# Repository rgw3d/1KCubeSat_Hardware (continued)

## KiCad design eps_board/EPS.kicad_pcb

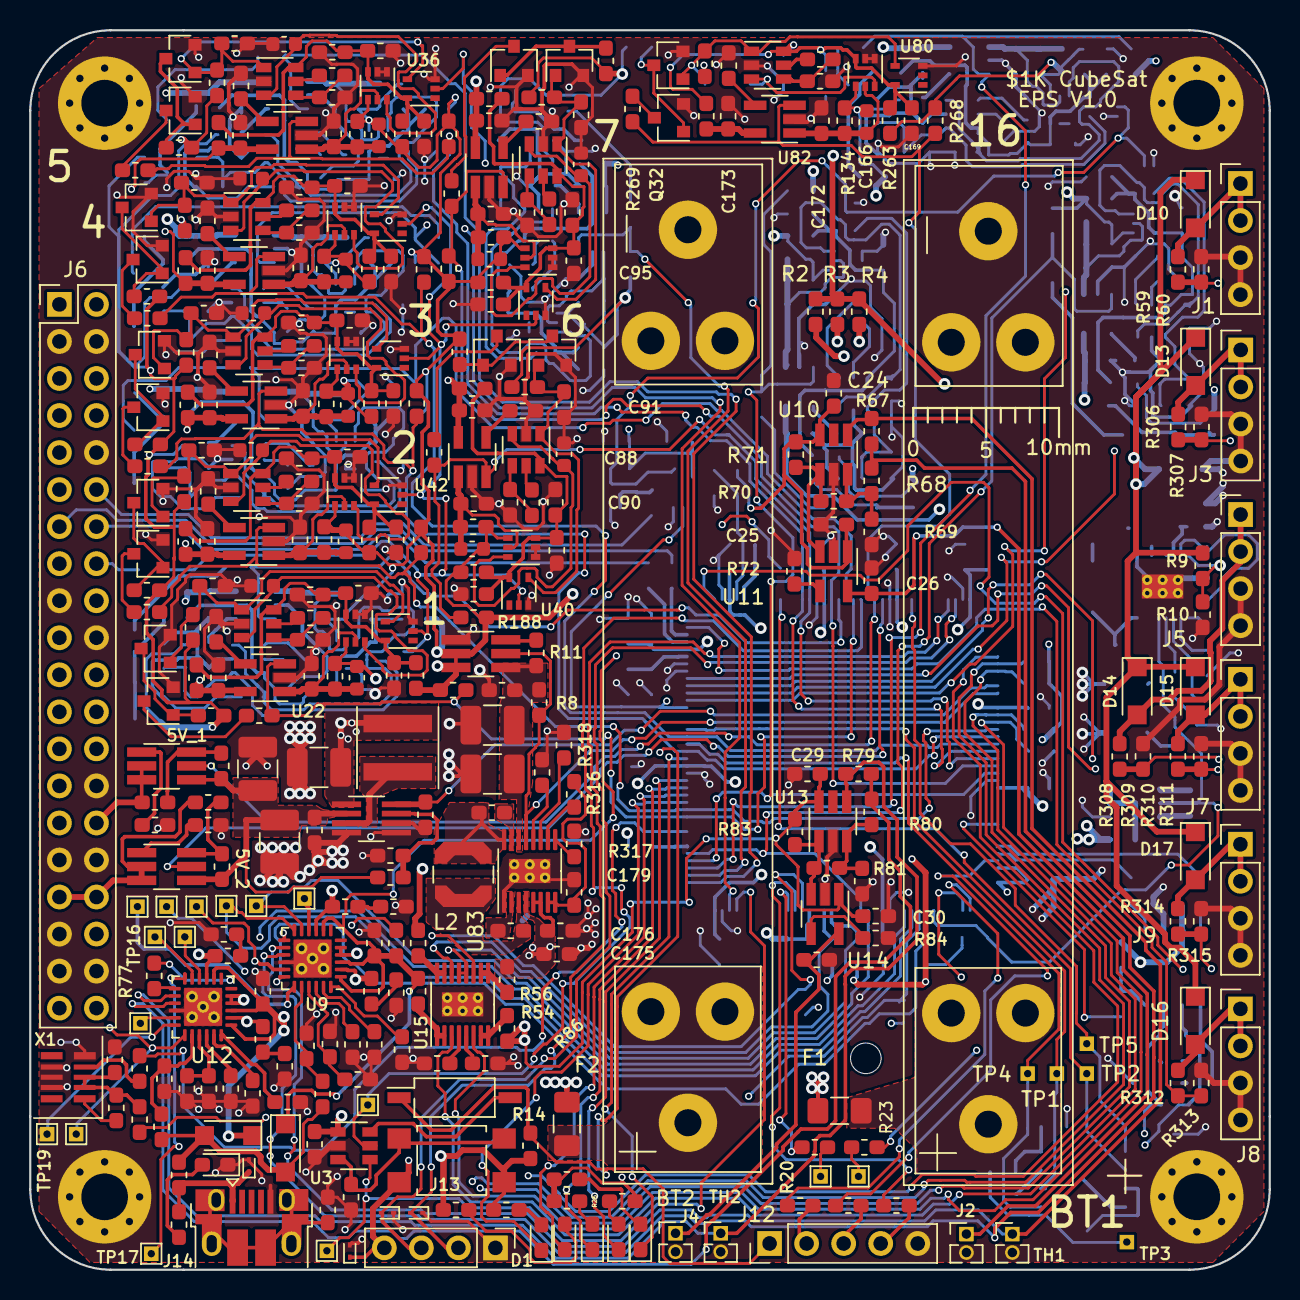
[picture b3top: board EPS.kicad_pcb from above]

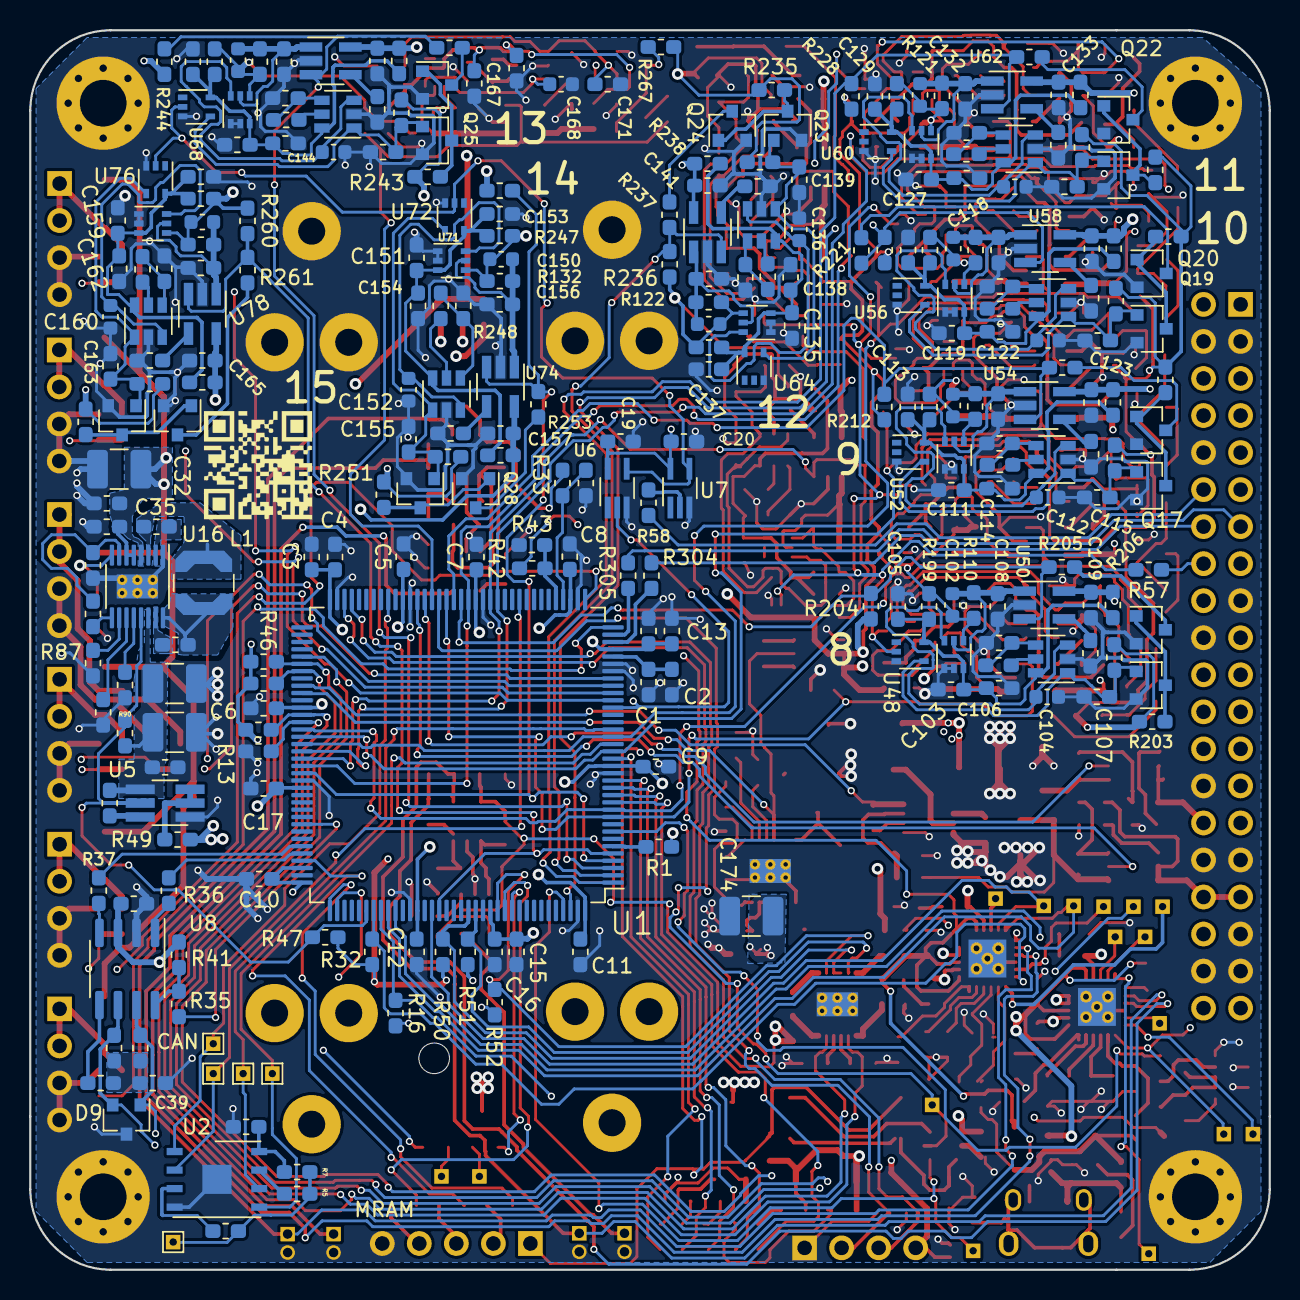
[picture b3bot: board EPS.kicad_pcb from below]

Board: 4 copper layers, 85.0 x 85.0 mm, 656 parts (279 on the bottom side), 356 nets.

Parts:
BT1, BT2: Battery_Cell; BatteryHolder_Keystone_54_v2_1x18650
C1, C2, C13: 0.01uF; C_0603_1608Metric_Pad1.05x0.95mm_HandSolder
C3, C15, C22, C25, C27, C30, C33, C40, C52, C60, C68, C76, C84, C92, C100, C108, C116, C124, C132, C140, C148, C156, C164, C172, C175, C179, C187, C188, C189, C190, C191, C192: 4.7uF; C_0603_1608Metric_Pad1.05x0.95mm_HandSolder
C4, C5, C6, C7, C8, C9, C10, C11, C12, C16, C17, C18, C19, C20, C21, C24, C26, C29, C31, C36, C38, C47, C49, C50, C53, C55, C57, C58, C61, C63, C65, C66, C69, C71, C73, C74, C77, C79, C81, C82, C85, C87, C89, C90, C93, C95, C97, C98, C101, C103, C105, C106, C109, C111, C113, C114, C117, C119, C121, C122, C125, C127, C129, C130, C133, C135, C137, C138, C141, C143, C145, C146, C149, C151, C153, C154, C157, C159, C161, C162, C165, C167, C169, C170, C173: 0.1uF; C_0603_1608Metric_Pad1.05x0.95mm_HandSolder
C14, C34, C44, C45, C51, C59, C67, C75, C83, C91, C99, C107, C115, C123, C131, C139, C147, C155, C163, C171, C176, C184: 1uF; C_0603_1608Metric_Pad1.05x0.95mm_HandSolder
C23, C28, C43, C182: DNP; C_0603_1608Metric_Pad1.05x0.95mm_HandSolder
C32, C41, C174, C180, C183, C185: 47uF; C_1210_3225Metric_Pad1.42x2.65mm_HandSolder
C35, C37, C177, C178: 22nF; C_0603_1608Metric_Pad1.05x0.95mm_HandSolder
C39: 4.7nF; C_0603_1608Metric_Pad1.05x0.95mm_HandSolder
C42, C181, C186: DNP; C_1210_3225Metric_Pad1.42x2.65mm_HandSolder
C46, C48, C54, C56, C62, C64, C70, C72, C78, C80, C86, C88, C94, C96, C102, C104, C110, C112, C118, C120, C126, C128, C134, C136, C142, C144, C150, C152, C158, C160, C166, C168: DNP; C_0603_1608Metric
D1, D19: LED_SMD_RED; LED_0603_1608Metric_Pad1.05x0.95mm_HandSolder
D2: LED_SMD_GREEN; LED_0603_1608Metric_Pad1.05x0.95mm_HandSolder
D3, D4, D5: LED_SMD_YELLOW; LED_0603_1608Metric_Pad1.05x0.95mm_HandSolder
D6, D7, D8, D18: ESD9B5.0ST5G; D_SOD-923
D9: NUP2105L; SOT-23
D10, D11, D12, D13, D14, D15, D16, D17: NRVB120VLSFT1G; D_SOD-123FL_handsolder
F1, F2: Polyfuse; Fuse_1206_3216Metric_Pad1.42x1.75mm_HandSolder
FID4: Fiducial; Gauge_10mm_Type1_SilkScreenTop
H1: MountingHole; MountingHole_2.1mm
H2, H3, H4, H5: MountingHole_Pad; MountingHole_3.2mm_M3_Pad_Via
J1, J3, J5, J7, J8, J9: Conn_01x04; PinHeader_1x04_P2.54mm_Vertical
J2, J4: Conn_01x02_Female; PinHeader_1x02_P1.27mm_Vertical
J6: Conn_02x20_Odd_Even; PinHeader_2x20_P2.54mm_Vertical
J12: Conn_01x05; PinHeader_1x05_P2.54mm_Vertical
J13: Conn_01x04_Male; PinHeader_1x04_P2.54mm_Vertical
J14: USB_B_Micro; USB_Micro-B_Amphenol_10103594-0001LF_Horizontal
L1, L2: 4.7uH; L_Coilcraft_LPS4018
L3: 2.2uH; L_Coilcraft_XAL5030
Q1, Q2, Q3, Q4, Q5, Q6, Q7, Q8, Q9, Q10, Q11, Q12, Q13, Q14, Q15, Q16, Q17, Q18, Q19, Q20, Q21, Q22, Q23, Q24, Q25, Q26, Q27, Q28, Q29, Q30, Q31, Q32: 2N7002K; SOT-23
R1, R29, R30, R31, R35, R36, R37, R38, R57, R58, R87, R88, R89, R90, R143, R149, R151, R157, R159, R165, R167, R173, R175, R181, R183, R189, R191, R197, R199, R205, R207, R213, R215, R221, R223, R229, R231, R237, R239, R245, R247, R253, R255, R261, R263, R269, R304, R305, R316, R317, R318, R319, R327: 0; R_0603_1608Metric_Pad1.05x0.95mm_HandSolder
R2, R3, R4, R7, R49, R53, R54, R55, R56, R328: 10m; R_0603_1608Metric_Pad1.05x0.95mm_HandSolder
R5, R6, R8, R10, R12, R13, R14, R16, R17, R18, R32, R33, R41, R42, R46, R47, R50, R51, R52, R59, R60, R65, R68, R77, R80, R144, R152, R160, R168, R176, R184, R192, R200, R208, R216, R224, R232, R240, R248, R256, R264, R306, R307, R308, R309, R310, R311, R312, R313, R314, R315, R320: 100K; R_0603_1608Metric_Pad1.05x0.95mm_HandSolder
R9: 224K; R_0603_1608Metric_Pad1.05x0.95mm_HandSolder
R11, R48, R62, R64, R66, R67, R74, R76, R78, R79, R97, R98: 10K; R_0603_1608Metric_Pad1.05x0.95mm_HandSolder
R15: 8.85K; R_0603_1608Metric_Pad1.05x0.95mm_HandSolder
R19, R20, R21, R22, R23: 49.9; R_0603_1608Metric_Pad1.05x0.95mm_HandSolder
R24, R25, R26, R27, R28, R329: 330; R_0603_1608Metric_Pad1.05x0.95mm_HandSolder
R34, R43: 150K; R_0603_1608Metric_Pad1.05x0.95mm_HandSolder
R39, R40: 60.4; R_0603_1608Metric_Pad1.05x0.95mm_HandSolder
R61, R73: 26.7K; R_0603_1608Metric_Pad1.05x0.95mm_HandSolder
R63, R71, R75, R83, R145, R147, R148, R153, R155, R156, R161, R163, R164, R169, R171, R172, R177, R179, R180, R185, R187, R188, R193, R195, R196, R201, R203, R204, R209, R211, R212, R217, R219, R220, R225, R227, R228, R233, R235, R236, R241, R243, R244, R249, R251, R252, R257, R259, R260, R265, R267, R268, R321: 1M; R_0603_1608Metric_Pad1.05x0.95mm_HandSolder
R69, R81: 280K; R_0603_1608Metric_Pad1.05x0.95mm_HandSolder
R70, R82, R150, R158, R166, R174, R182, R190, R198, R206, R214, R222, R230, R238, R246, R254, R262, R270: DNP; R_0603_1608Metric_Pad1.05x0.95mm_HandSolder
R72, R84, R100, R102, R104, R106, R112, R114, R116, R118, R124, R126, R128, R130, R136, R138, R140, R142: 3.09K; R_0603_1608Metric_Pad1.05x0.95mm_HandSolder
R85, R86: 150; R_0603_1608Metric_Pad1.05x0.95mm_HandSolder
R91, R92: 1K; R_0603_1608Metric_Pad1.05x0.95mm_HandSolder
R93, R95, R96, R107, R108, R109, R110, R119, R120, R121, R122, R131, R132, R133, R134: 0.1; R_0603_1608Metric_Pad1.05x0.95mm_HandSolder
R94: 0.039; R_0603_1608Metric_Pad1.05x0.95mm_HandSolder
R99: 20K; R_0603_1608Metric_Pad1.05x0.95mm_HandSolder
R101, R103, R105, R123, R125, R127, R129, R135, R137, R139, R141: 140K; R_0603_1608Metric_Pad1.05x0.95mm_HandSolder
R111, R117: 698K; R_0603_1608Metric_Pad1.05x0.95mm_HandSolder
R113, R115: 1.5M; R_0603_1608Metric_Pad1.05x0.95mm_HandSolder
R322: 137K; R_0603_1608Metric_Pad1.05x0.95mm_HandSolder
R323, R324, R325, R326: 1; R_0603_1608Metric_Pad1.05x0.95mm_HandSolder
SW1: SW_DIP_x01; SW_DIP_SPSTx01_Slide_Copal_CHS-01B_W7.62mm_P1.27mm
SW2: SW_Push; SW_SPST_TL3305A
TH1, TH2: Thermistor_NTC; PinHeader_1x02_P1.27mm_Vertical
TP1, TP2, TP3, TP4, TP5, TP8, TP9: TP_smt_1x1; TestPoint_THTPad_1.0x1.0mm_Drill0.5mm
TP7, TP10, TP11, TP12, TP13, TP14, TP15, TP16, TP17, TP18, TP19, TP20: TP_1x1; TestPoint_THTPad_1.0x1.0mm_Drill0.5mm
TP37, TP39: TP_1.5x1.5; TestPoint_THTPad_1.0x1.0mm_Drill0.5mm
U1: STM32L496ZGTx; LQFP-144_20x20mm_P0.5mm
U2: MR25H10; DFN-8-1EP_6x5mm_P1.27mm_EP2x2mm
U3: TPL5010; SOT-23-6
U4, U5, U17, U18: TPS270; TSOT-23-6_HandSoldering
U6, U7: 74LVC1G07; SOT-353_SC-70-5_Handsoldering
U8: SN65HVD230; SOIC-8_3.9x4.9mm_P1.27mm
U9, U12: LTC4066; QFN-24-1EP_4x4mm_P0.5mm_EP2.6x2.6mm_0.4mmThermalVias
U10, U13: MCP65R46; SOT-23-6_Handsoldering
U11, U14, U22, U26, U30, U34, U38, U42, U46, U50, U54, U58, U62, U66, U70, U74, U78, U82: FPF2123; SOT-23-5_HandSoldering
U15: LTC4415; MSOP-16-1EP_3x4.039mm_P0.5mm_EP1.651x2.845mm_0.3mmThermalVi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
U16, U83: LTC3130-1; MSOP-16-1EP_3x4.039mm_P0.5mm_EP1.651x2.845mm_0.3mmThermalVi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
U19, U23, U27, U31, U35, U39, U43, U47, U51, U55, U59, U63, U67, U71, U75, U79: NCS211; SOT-363_SC-70-6
U20, U24, U28, U32, U36, U40, U44, U48, U52, U56, U60, U64, U68, U72, U76, U80: 74LVC1G07; SOT-353_SC-70-5
U21, U25, U29, U33, U37, U41, U45, U49, U53, U57, U61, U65, U69, U73, U77, U81: MCP65R46; SOT-23-6
U84: MP3414A; TSOT-23-8_HandSoldering
X1: TG-3541CE; Oscillator_SMD_SeikoEpson_TG3541CE-10Pin_3.2x2.5mm_HandSold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

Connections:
+3V3: C19.2, C20.2, C46.2, C54.2, C62.2, C70.2, C78.2, C86.2, C94.2, C102.2, C110.2, C118.2, C126.2, C134.2, C142.2, C150.2, C158.2, C166.2, R93.2, R94.2, R95.2, R96.2, R107.2, R108.2, R109.2, R110.2, R119.2, R120.2, R121.2, R122.2, R131.2, R132.2, R133.2, R134.2, R143.2, R145.2, R147.2, R148.2, R151.2, R153.2, R155.2, R156.2, R159.2, R161.2, R163.2, R164.2, R167.2, R169.2, R171.2, R172.2, R175.2, R177.2, R179.2, R180.2, R183.2, R185.2, R187.2, R188.2, R191.2, R193.2, R195.2, R196.2, R199.2, R201.2, R203.2, R204.2, R207.2, R209.2, R211.2, R212.2, R215.2, R217.2, R219.2, R220.2, R223.2, R225.2, R227.2, R228.2, R231.2, R233.2, R235.2, R236.2, R239.2, R241.2, R243.2, R244.2, R247.2, R249.2, R251.2, R252.2, R255.2, R257.2, R259.2, R260.2, R263.2, R265.2, R267.2, R268.2, U4.2, U4.3, U6.5, U7.5, U19.4, U23.4, U27.4, U31.4, U35.4, U39.4, U43.4, U47.4, U51.4, U55.4, U59.4, U63.4, U67.4, U71.4, U75.4, U79.4
+5V: C184.1, C185.1, C186.1, R97.2, R98.2, R321.2, U17.4, U18.4, U84.2
/3.3V_9: C117.2, J6.9, R214.1, U54.5
/3.3V_10: C125.2, J6.6, R222.1, U58.5
/3.3V_11: C133.2, J6.1, R230.1, U62.5
/3.3V_12: C141.2, J6.18, R238.1, U66.5
/3.3V_16: C173.2, R270.1, U82.5
/3.3V_ACS_LOGIC: C85.2, J6.2, R182.1, U38.5
/3.3V_AVI_CAN: C77.2, J6.5, R174.1, U34.5
/3.3V_CLK: C109.2, J6.25, R206.1, U50.5
/3.3V_EPS_CAN: C38.1, C157.2, R41.1, R254.1, U8.3, U74.5
/3.3V_EPS_MRAM: C165.2, R5.1, R6.1, R7.2, R262.1, TP3.1, U78.5
/3.3V_EPS_STM: C21.1, C149.2, D6.1, J13.4, R2.1, R3.1, R4.1, R12.2, R14.1, R16.2, R18.2, R24.1, R25.1, R26.1, R27.1, R28.1, R30.2, R32.2, R46.2, R47.2, R50.1, R51.1, R52.1, R246.1, SW2.1, U3.1, U70.5
/3.3V_GPS: C61.2, J6.24, R158.1, U26.5
/3.3V_GYRO: C93.2, J6.23, R190.1, U42.5
/3.3V_MAG: C101.2, J6.8, R198.1, U46.5
/3.3V_MRAM: C69.2, J6.11, R166.1, U30.5
/3.3V_STM_CORE: C53.2, J6.26, R150.1, U22.5
/5V0_1: C44.1, J6.30, U17.2, U17.3
/5V0_2: C45.1, J6.33, J6.34, U18.2, U18.3
/AVI_EXTRN_RST: R57.2, U20.2, U24.2, U28.2, U32.2, U36.2, U40.2, U44.2, U48.2
/BATTERY/NTC: R67.2, TH1.1, U9.14, U10.4
/BATTERY/VNTC: R67.1, R68.1, U9.15
/BATTERY_CHARGER/BAT: C189.1, F1.1, U9.2, U9.4, U9.5
/BC_1_CLDIS: TP7.1, U9.10
/BC_1_ISTAT: R66.2, U9.24
/BC_1_POL: R46.1, TP12.1, U1.78, U9.19
/BC_1_SHDN: TP11.1, U1.117, U9.12
/BC_1_SUSP: TP10.1, U1.123, U9.11
/BC_2_CLDIS: TP15.1, U12.10
/BC_2_ISTAT: R78.2, U12.24
/BC_2_POL: R18.1, TP18.1, U1.79, U12.19
/BC_2_SHDN: TP17.1, U1.118, U12.12
/BC_2_SUSP: TP16.1, U1.77, U12.11
/CANH: D9.1, J6.40, R39.1, U8.7
/CANL: D9.2, J6.39, R40.2, U8.6
/CURRENT_MONITORS/PWR1_8_ON: R204.1, R205.1, U1.54, U50.3
/CURRENT_MONITORS/PWR1_9_ON: R212.1, R213.1, U1.55, U54.3
/CURRENT_MONITORS/PWR1_10_ON: R220.1, R221.1, U1.142, U58.3
/CURRENT_MONITORS/PWR1_11_ON: R228.1, R229.1, U1.1, U62.3
/CURRENT_MONITORS/PWR1_12_ON: R236.1, R237.1, U1.2, U66.3
/CURRENT_MONITORS/PWR1_13_ON: R244.1, R245.1, U1.3, U70.3
/CURRENT_MONITORS/PWR1_16_ON: R268.1, R269.1, U1.58, U82.3
/CURRENT_MONITORS/PWR2_1_ON: U1.59, U17.5
/CURRENT_MONITORS/PWR2_2_ON: U1.60, U18.5
/CURRENT_MONITORS/RST1_13: U6.4, U7.4, U68.2, U72.2, U76.2
/CURRENT_MONITORS/sheet601A160D/ISET+: R100.2, U22.4
/CURRENT_MONITORS/sheet601A160D/RREF+: R99.2, U21.5
/CURRENT_MONITORS/sheet601A160D/RREF-: R99.1, R144.2, U21.4
/CURRENT_MONITORS/sheet601A160D/SHUNT-: C46.1, C52.2, R93.1, U19.5, U22.1
/CURRENT_MONITORS/sheet620B1C5A/ISET+: R138.2, U74.4
/CURRENT_MONITORS/sheet620B1C5A/RREF+: R137.2, U73.5
/CURRENT_MONITORS/sheet620B1C5A/RREF-: R137.1, R248.2, U73.4
/CURRENT_MONITORS/sheet620B1C5A/SHUNT-: C150.1, C156.2, R132.1, U71.5, U74.1
/CURRENT_MONITORS/sheet620B1C5B/ISET+: R140.2, U78.4
/CURRENT_MONITORS/sheet620B1C5B/RREF+: R139.2, U77.5
/CURRENT_MONITORS/sheet620B1C5B/RREF-: R139.1, R256.2, U77.4
/CURRENT_MONITORS/sheet620B1C5B/SHUNT-: C158.1, C164.2, R133.1, U75.5, U78.1
/CURRENT_MONITORS/sheet620B1C5C/ISET+: R142.2, U82.4
/CURRENT_MONITORS/sheet620B1C5C/RREF+: R141.2, U81.5
/CURRENT_MONITORS/sheet620B1C5C/RREF-: R141.1, R264.2, U81.4
/CURRENT_MONITORS/sheet620B1C5C/SHUNT-: C166.1, C172.2, R134.1, U79.5, U82.1
/CURRENT_MONITORS/sheet620B1C59/ISET+: R136.2, U70.4
/CURRENT_MONITORS/sheet620B1C59/RREF+: R135.2, U69.5
/CURRENT_MONITORS/sheet620B1C59/RREF-: R135.1, R240.2, U69.4
/CURRENT_MONITORS/sheet620B1C59/SHUNT-: C142.1, C148.2, R131.1, U67.5, U70.1
/CURRENT_MONITORS/sheet6206D7D7/ISET+: R106.2, U34.4
/CURRENT_MONITORS/sheet6206D7D7/RREF+: R105.2, U33.5
/CURRENT_MONITORS/sheet6206D7D7/RREF-: R105.1, R168.2, U33.4
/CURRENT_MONITORS/sheet6206D7D7/SHUNT-: C70.1, C76.2, R96.1, U31.5, U34.1
/CURRENT_MONITORS/sheet6209BA5A/ISET+: R128.2, U62.4
/CURRENT_MONITORS/sheet6209BA5A/RREF+: R127.2, U61.5
/CURRENT_MONITORS/sheet6209BA5A/RREF-: R127.1, R224.2, U61.4
/CURRENT_MONITORS/sheet6209BA5A/SHUNT-: C126.1, C132.2, R121.1, U59.5, U62.1
/CURRENT_MONITORS/sheet6209BA5B/ISET+: R130.2, U66.4
/CURRENT_MONITORS/sheet6209BA5B/RREF+: R129.2, U65.5
/CURRENT_MONITORS/sheet6209BA5B/RREF-: R129.1, R232.2, U65.4
/CURRENT_MONITORS/sheet6209BA5B/SHUNT-: C134.1, C140.2, R122.1, U63.5, U66.1
/CURRENT_MONITORS/sheet6209BA58/ISET+: R124.2, U54.4
/CURRENT_MONITORS/sheet6209BA58/RREF+: R123.2, U53.5
/CURRENT_MONITORS/sheet6209BA58/RREF-: R123.1, R208.2, U53.4
/CURRENT_MONITORS/sheet6209BA58/SHUNT-: C110.1, C116.2, R119.1, U51.5, U54.1
/CURRENT_MONITORS/sheet6209BA59/ISET+: R126.2, U58.4
/CURRENT_MONITORS/sheet6209BA59/RREF+: R125.2, U57.5
/CURRENT_MONITORS/sheet6209BA59/RREF-: R125.1, R216.2, U57.4
/CURRENT_MONITORS/sheet6209BA59/SHUNT-: C118.1, C124.2, R120.1, U55.5, U58.1
/CURRENT_MONITORS/sheet62057B58/ISET+: R104.2, U30.4
/CURRENT_MONITORS/sheet62057B58/RREF+: R103.2, U29.5
/CURRENT_MONITORS/sheet62057B58/RREF-: R103.1, R160.2, U29.4
/CURRENT_MONITORS/sheet62057B58/SHUNT-: C62.1, C68.2, R95.1, U27.5, U30.1
/CURRENT_MONITORS/sheet6204228E/ISET+: R102.2, U26.4
/CURRENT_MONITORS/sheet6204228E/RREF+: R101.2, U25.5
/CURRENT_MONITORS/sheet6204228E/RREF-: R101.1, R152.2, U25.4
/CURRENT_MONITORS/sheet6204228E/SHUNT-: C54.1, C60.2, R94.1, U23.5, U26.1
/CURRENT_MONITORS/sheet6208477B/ISET+: R112.2, U38.4
/CURRENT_MONITORS/sheet6208477B/RREF+: R111.2, U37.5
/CURRENT_MONITORS/sheet6208477B/RREF-: R111.1, R176.2, U37.4
/CURRENT_MONITORS/sheet6208477B/SHUNT-: C78.1, C84.2, R107.1, U35.5, U38.1
/CURRENT_MONITORS/sheet6208477C/ISET+: R114.2, U42.4
/CURRENT_MONITORS/sheet6208477C/RREF+: R113.2, U41.5
/CURRENT_MONITORS/sheet6208477C/RREF-: R113.1, R184.2, U41.4
/CURRENT_MONITORS/sheet6208477C/SHUNT-: C86.1, C92.2, R108.1, U39.5, U42.1
/CURRENT_MONITORS/sheet6208477D/ISET+: R116.2, U46.4
/CURRENT_MONITORS/sheet6208477D/RREF+: R115.2, U45.5
/CURRENT_MONITORS/sheet6208477D/RREF-: R115.1, R192.2, U45.4
/CURRENT_MONITORS/sheet6208477D/SHUNT-: C94.1, C100.2, R109.1, U43.5, U46.1
/CURRENT_MONITORS/sheet6208477E/ISET+: R118.2, U50.4
/CURRENT_MONITORS/sheet6208477E/RREF+: R117.2, U49.5
/CURRENT_MONITORS/sheet6208477E/RREF-: R117.1, R200.2, U49.4
/CURRENT_MONITORS/sheet6208477E/SHUNT-: C102.1, C108.2, R110.1, U47.5, U50.1
/EPS_EXTRN_RST: R58.2, U7.2
/EPS_WATCHDOG: J12.1, R14.2, SW1.1, U1.25, U6.2
/HPWR_EN: R320.2, U1.81, U84.8
/IDEAL_EN1: R12.1, U1.85, U15.3
/INTERBOARD_CONNECTOR/AVI_RESET: J6.16, R57.1
/INTERBOARD_CONNECTOR/EPS_RESET: J6.12, R58.1
/PG_3V3: R8.1, U1.82, U4.5, U83.13
/PG_SOLAR: R17.1, R47.1, U1.114, U5.5, U16.13
/PMIC/ADC1_IN9: R33.2, R34.2, U1.40
/PMIC/ADC1_IN10: R42.2, R43.2, U1.41
/PMIC/CAN1_RX: R37.2, U1.103
/PMIC/CAN1_TX: R36.2, U1.104
/PMIC/CAN_RS: R35.2, U1.100
/PMIC/CAN_TRANSCEIVER/Vref: R38.2, U8.5
/PMIC/INT_1: R148.1, R149.1, U1.10, U1.56, U22.3
/PMIC/INT_2: R156.1, R157.1, U1.11, U1.87, U26.3
/PMIC/INT_3: R164.1, R165.1, U1.19, U1.88, U30.3
/PMIC/INT_4: R172.1, R173.1, U1.21, U1.89, U34.3
/PMIC/INT_5: R180.1, R181.1, U1.49, U1.90, U38.3
/PMIC/INT_6: R188.1, R189.1, U1.50, U1.91, U42.3
/PMIC/INT_7: R196.1, R197.1, U1.53, U1.92, U46.3
/PMIC/INT_8: R252.1, R253.1, U1.4, U1.93, U74.3
/PMIC/INT_9: R260.1, R261.1, U1.5, U1.124, U78.3
/PMIC/JTCK_SWCLK: R20.1, U1.109
/PMIC/JTDI: R23.1, U1.110
/PMIC/JTDO_TRACESWO: R22.1, U1.133
/PMIC/JTMS_SWDIO: R21.1, U1.105
/PMIC/LED_1: D1.1, U1.12
/PMIC/LED_2: D2.1, U1.13
/PMIC/LED_3: D3.1, U1.14
/PMIC/LED_4: D4.1, U1.15
/PMIC/LED_5: D5.1, U1.18
/PMIC/LPUART1_RX: D8.2, J13.2, U1.69
/PMIC/LPUART1_TX: D7.2, J13.3, U1.70
/PMIC/NJRST: R19.1, U1.134
/PMIC/OSC32_TCXO/OE: R31.1, X1.1
/PMIC/QUADSPI_BK1_IO0: TP4.1, U1.20, U2.5
/PMIC/QUADSPI_BK1_IO1: TP2.1, U1.46, U2.2
/PMIC/QUADSPI_BK1_NCS: TP5.1, U1.64, U2.1
/PMIC/QUADSPI_CLK: TP1.1, U1.22, U2.6
/PMIC/RCC_OSC32_IN: R29.2, U1.8
/PMIC/UART4_RX: R305.2, U1.35
/PMIC/UART4_TX: R304.2, U1.34
/PMIC/WATCHDOG_DONE: TP9.1, U1.141, U3.4
/PMIC/WATCHDOG_WAKE: TP8.1, U1.57, U3.5
/SOLAR_5V: C187.1, C190.1, R49.1, U9.9, U12.9
/SOLAR_ADC1: R59.2, R60.1, U1.26
/SOLAR_ADC2: R306.2, R307.1, U1.27
/SOLAR_ADC3: R308.2, R309.1, U1.28
/SOLAR_ADC4: R310.2, R311.1, U1.29
/SOLAR_ADC5: R312.2, R313.1, U1.36
/SOLAR_ADC6: R314.2, R315.1, U1.37
/SOLAR_MPPT_5V/MPPC: R9.2, R10.2, U16.8
/SOLAR_MPPT_5V/VCC: C40.1, R88.2, U16.7
/SOLAR_MPPT_5V/VOUT: C41.1, C42.1, C43.1, R17.2, R48.2, U5.4, U16.14
/UART_RXI: J6.13, R305.1
/UART_TXO: J6.14, R304.1
/VEXT: D11.2, D12.2, R61.2, R73.2, R328.1
/VOUT1: C24.1, C25.1, C188.1, D11.1, R33.1, R53.2, R65.2, R71.1, U9.1, U9.3, U9.8, U10.6, U11.1
/VOUT2: C29.1, C30.1, C191.1, D12.1, R42.1, R54.2, R77.2, R83.1, U12.1, U12.3, U12.8, U13.6, U14.1
/VRAW_SOLAR: C32.1, C33.1, C34.1, D10.1, D13.1, D14.1, D15.1, D16.1, D17.1, R9.1, U16.4, U16.5, U16.6
/sheet5F4CFCDE/BAT: C192.1, F2.1, U12.2, U12.4, U12.5
/sheet5F4CFCDE/NTC: R79.2, TH2.1, U12.14, U13.4
/sheet5F4CFCDE/VNTC: R79.1, R80.1, U12.15
/sheet5F71F776/VIN1: R53.1, U15.1, U15.2
/sheet5F71F776/VIN2: R54.1, U15.7, U15.8
/sheet5F71F776/VOUT1: R55.2, U15.15, U15.16
/sheet5F71F776/VOUT2: R56.2, U15.9, U15.10
/sheet5FCD3934/MPPC: C179.1, R316.2, U83.7, U83.8
/sheet5FCD3934/VOUT: C180.1, C181.1, C182.1, R8.2, R11.2, U4.4, U83.14
/~BC_1_CHRG: R32.1, TP13.1, U1.115, U9.18
/~BC_1_VEXT: TP14.1, U9.17
/~BC_2_CHRG: R16.1, TP19.1, U1.116, U12.18
/~BC_2_VEXT: TP20.1, U12.17
/~IDEAL_EN2: R13.2, U1.86, U15.6
/~IDEAL_STATUS1: R51.2, U1.129, U15.14
/~IDEAL_STATUS2: R52.2, U1.132, U15.11
/~IDEAL_WARN1: R50.2, U1.128, U15.12, U15.13
GND: BT1.2, BT2.2, C1.1, C2.1, C3.1, C4.2, C5.2, C6.2, C7.2, C8.2, C9.2, C10.2, C11.1, C12.1, C13.2, C14.2, C15.1, C16.1, C17.1, C18.2, C19.1, C20.1, C21.2, C22.2, C23.2, C24.2, C25.2, C26.2, C27.2, C28.2, C29.2, C30.2, C31.2, C32.2, C33.2, C34.2, C36.2, C38.2, C39.2, C40.2, C41.2, C42.2, C43.2, C47.2, C48.1, C49.1, C50.1, C51.1, C52.1, C53.1, C55.2, C56.1, C57.1, C58.1, C59.1, C60.1, C61.1, C63.2, C64.1, C65.1, C66.1, C67.1, C68.1, C69.1, C71.2, C72.1, C73.1, C74.1, C75.1, C76.1, C77.1, C79.2, C80.1, C81.1, C82.1, C83.1, C84.1, C85.1, C87.2, C88.1, C89.1, C90.1, C91.1, C92.1, C93.1, C95.2, C96.1, C97.1, C98.1, C99.1, C100.1, C101.1, C103.2, C104.1, C105.1, C106.1, C107.1, C108.1, C109.1, C111.2, C112.1, C113.1, C114.1, C115.1, C116.1, C117.1, C119.2, C120.1, C121.1, C122.1, C123.1, C124.1, C125.1, C127.2, C128.1, C129.1, C130.1, C131.1, C132.1, C133.1, C135.2, C136.1, C137.1, C138.1, C139.1, C140.1, C141.1, C143.2, C144.1, C145.1, C146.1, C147.1, C148.1, C149.1, C151.2, C152.1, C153.1, C154.1, C155.1, C156.1, C157.1, C159.2, C160.1, C161.1, C162.1, C163.1, C164.1, C165.1, C167.2, C168.1, C169.1, C170.1, C171.1, C172.1, C173.1, C174.2, C175.2, C176.2, C179.2, C180.2, C181.2, C182.2, C183.2, C184.2, C185.2, C186.2, C188.2, C191.2, D6.2, D7.1, D8.1, D9.3, D18.2, D19.1, H2.1, H3.1, H4.1, H5.1, J1.3, J1.4, J2.2, J3.3, J3.4, J4.2, J5.3, J5.4, J6.3, J6.4, J6.10, J6.17, J6.20, J6.28, J6.31, J6.32, J6.35, J6.37, J6.38, J7.3, J7.4, J8.3, J8.4, J9.3, J9.4, J12.5, J13.1, J14.5, Q1.2, Q2.2, Q3.2, Q4.2, Q5.2, Q6.2, Q7.2, Q8.2, Q9.2, Q10.2, Q11.2, Q12.2, Q13.2, Q14.2, Q15.2, Q16.2, Q17.2, Q18.2, Q19.2, Q20.2, Q21.2, Q22.2, Q23.2, Q24.2, Q25.2, Q26.2, Q27.2, Q28.2, Q29.2, Q30.2, Q31.2, Q32.2, R10.1, R13.1, R15.2, R34.1, R43.1, R60.2, R62.1, R63.1, R64.1, R66.1, R69.2, R72.1, R74.1, R75.1, R76.1, R78.1, R81.2, R84.1, R85.2, R86.2, R87.2, R89.2, R90.1, R91.1, R92.1, R100.1, R102.1, R104.1, R106.1, R112.1, R114.1, R116.1, R118.1, R124.1, R126.1, R128.1, R130.1, R136.1, R138.1, R140.1, R142.1, R144.1, R152.1, R160.1, R168.1, R176.1, R184.1, R192.1, R200.1, R208.1, R216.1, R224.1, R232.1, R240.1, R248.1, R256.1, R264.1, R307.2, R309.2, R311.2, R313.2, R315.2, R317.2, R318.2, R319.1, R320.1, R322.1, R323.2, R324.1, R325.2, R326.1, R327.1, TH1.2, TH2.2, U1.16, U1.30, U1.31, U1.38, U1.51, U1.61, U1.71, U1.83, U1.94, U1.107, U1.120, U1.130, U1.143, U2.4, U2.9, U3.2, U4.1, U5.1, U6.3, U7.3, U8.2, U9.16, U9.25, U10.2, U11.2, U12.16, U12.25, U13.2, U14.2, U15.17, U16.1, U16.17, U19.1, U19.2, U20.3, U21.2, U22.2, U23.1, U23.2, U24.3, U25.2, U26.2, U27.1, U27.2, U28.3, U29.2, U30.2, U31.1, U31.2, U32.3, U33.2, U34.2, U35.1, U35.2, U36.3, U37.2, U38.2, U39.1, U39.2, U40.3, U41.2, U42.2, U43.1, U43.2, U44.3, U45.2, U46.2, U47.1, U47.2, U48.3, U49.2, U50.2, U51.1, U51.2, U52.3, U53.2, U54.2, U55.1, U55.2, U56.3, U57.2, U58.2, U59.1, U59.2, U60.3, U61.2, U62.2, U63.1, U63.2, U64.3, U65.2, U66.2, U67.1, U67.2, U68.3, U69.2, U70.2, U71.1, U71.2, U72.3, U73.2, U74.2, U75.1, U75.2, U76.3, U77.2, U78.2, U79.1, U79.2, U80.3, U81.2, U82.2, U83.1, U83.17, U84.4, U84.5, U84.6, X1.5, X1.7, X1.8, X1.9
unnamed: BT1.1, F1.2
unnamed: BT2.1, F2.2
unnamed: C1.2, C2.2, U1.32
unnamed: C3.2, C4.1, C5.1, C6.1, C7.1, C8.1, C9.1, C10.1, C11.2, C12.2, R1.2, R2.2, U1.17, U1.39, U1.52, U1.62, U1.72, U1.84, U1.106, U1.108, U1.121, U1.144
unnamed: C13.1, C14.1, R3.2, U1.33
unnamed: C15.2, C16.2, C17.2, R4.2, U1.95, U1.131
unnamed: C18.1, R7.1, U2.8
unnamed: C22.1, C23.1, U9.21
unnamed: C26.1, J2.1, U11.5
unnamed: C27.1, C28.1, U12.21
unnamed: C31.1, J4.1, U14.5
unnamed: C35.1, L1.1, U16.3
unnamed: C35.2, U16.2
unnamed: C36.1, R30.1, R31.2, X1.2, X1.3
unnamed: C37.1, U16.15
unnamed: C37.2, L1.2, U16.16
unnamed: C39.1, R38.1, R39.2, R40.1
unnamed: C44.2, R97.1, U17.6
unnamed: C45.2, R98.1, U18.6
unnamed: C47.1, C49.2, C50.2, R143.1, R150.2, U19.3, U20.5, U21.6
unnamed: C48.2, U19.6, U21.3
unnamed: C51.2, Q1.1, R145.1, U20.4, U21.1
unnamed: C55.1, C57.2, C58.2, R151.1, R158.2, U23.3, U24.5, U25.6
unnamed: C56.2, U23.6, U25.3
unnamed: C59.2, Q3.1, R153.1, U24.4, U25.1
unnamed: C63.1, C65.2, C66.2, R159.1, R166.2, U27.3, U28.5, U29.6
unnamed: C64.2, U27.6, U29.3
unnamed: C67.2, Q5.1, R161.1, U28.4, U29.1
unnamed: C71.1, C73.2, C74.2, R167.1, R174.2, U31.3, U32.5, U33.6
unnamed: C72.2, U31.6, U33.3
unnamed: C75.2, Q7.1, R169.1, U32.4, U33.1
unnamed: C79.1, C81.2, C82.2, R175.1, R182.2, U35.3, U36.5, U37.6
unnamed: C80.2, U35.6, U37.3
unnamed: C83.2, Q9.1, R177.1, U36.4, U37.1
unnamed: C87.1, C89.2, C90.2, R183.1, R190.2, U39.3, U40.5, U41.6
unnamed: C88.2, U39.6, U41.3
unnamed: C91.2, Q11.1, R185.1, U40.4, U41.1
unnamed: C95.1, C97.2, C98.2, R191.1, R198.2, U43.3, U44.5, U45.6
unnamed: C96.2, U43.6, U45.3
unnamed: C99.2, Q13.1, R193.1, U44.4, U45.1
unnamed: C103.1, C105.2, C106.2, R199.1, R206.2, U47.3, U48.5, U49.6
unnamed: C104.2, U47.6, U49.3
unnamed: C107.2, Q15.1, R201.1, U48.4, U49.1
unnamed: C111.1, C113.2, C114.2, R207.1, R214.2, U51.3, U52.5, U53.6
unnamed: C112.2, U51.6, U53.3
unnamed: C115.2, Q17.1, R209.1, U52.4, U53.1
unnamed: C119.1, C121.2, C122.2, R215.1, R222.2, U55.3, U56.5, U57.6
unnamed: C120.2, U55.6, U57.3
unnamed: C123.2, Q19.1, R217.1, U56.4, U57.1
unnamed: C127.1, C129.2, C130.2, R223.1, R230.2, U59.3, U60.5, U61.6
unnamed: C128.2, U59.6, U61.3
unnamed: C131.2, Q21.1, R225.1, U60.4, U61.1
unnamed: C135.1, C137.2, C138.2, R231.1, R238.2, U63.3, U64.5, U65.6
unnamed: C136.2, U63.6, U65.3
unnamed: C139.2, Q23.1, R233.1, U64.4, U65.1
unnamed: C143.1, C145.2, C146.2, R239.1, R246.2, U67.3, U68.5, U69.6
unnamed: C144.2, U67.6, U69.3
unnamed: C147.2, Q25.1, R241.1, U68.4, U69.1
unnamed: C151.1, C153.2, C154.2, R247.1, R254.2, U71.3, U72.5, U73.6
unnamed: C152.2, U71.6, U73.3
unnamed: C155.2, Q27.1, R249.1, U72.4, U73.1
unnamed: C159.1, C161.2, C162.2, R255.1, R262.2, U75.3, U76.5, U77.6
unnamed: C160.2, U75.6, U77.3
unnamed: C163.2, Q29.1, R257.1, U76.4, U77.1
unnamed: C167.1, C169.2, C170.2, R263.1, R270.2, U79.3, U80.5, U81.6
unnamed: C168.2, U79.6, U81.3
unnamed: C171.2, Q31.1, R265.1, U80.4, U81.1
unnamed: C177.1, L2.1, U83.3
unnamed: C177.2, U83.2
unnamed: C178.1, U83.15
unnamed: C178.2, L2.2, U83.16
unnamed: C187.2, R323.1
unnamed: C189.2, R324.2
unnamed: C190.2, R325.1
unnamed: C192.2, R326.2
unnamed: D1.2, R24.2
unnamed: D2.2, R25.2
unnamed: D3.2, R26.2
unnamed: D4.2, R27.2
unnamed: D5.2, R28.2
unnamed: D10.2, J1.1, J1.2, R59.1
unnamed: D13.2, J3.1, J3.2, R306.1
unnamed: D14.2, J5.1, J5.2, R308.1
unnamed: D15.2, J7.1, J7.2, R310.1
unnamed: D16.2, J8.1, J8.2, R312.1
unnamed: D17.2, J9.1, J9.2, R314.1
unnamed: D18.1, J14.1, R328.2, R329.2
unnamed: D19.2, R329.1
unnamed: J12.2, R20.2
unnamed: J12.3, R21.2
unnamed: J12.4, R22.2
unnamed: J14.6, R327.2
unnamed: L3.1, U84.3
unnamed: Q1.3, Q2.1, R147.1
unnamed: Q2.3, R149.2
unnamed: Q3.3, Q4.1, R155.1
unnamed: Q4.3, R157.2
unnamed: Q5.3, Q6.1, R163.1
unnamed: Q6.3, R165.2
unnamed: Q7.3, Q8.1, R171.1
unnamed: Q8.3, R173.2
unnamed: Q9.3, Q10.1, R179.1
unnamed: Q10.3, R181.2
unnamed: Q11.3, Q12.1, R187.1
unnamed: Q12.3, R189.2
unnamed: Q13.3, Q14.1, R195.1
unnamed: Q14.3, R197.2
unnamed: Q15.3, Q16.1, R203.1
unnamed: Q16.3, R205.2
unnamed: Q17.3, Q18.1, R211.1
unnamed: Q18.3, R213.2
unnamed: Q19.3, Q20.1, R219.1
unnamed: Q20.3, R221.2
unnamed: Q21.3, Q22.1, R227.1
unnamed: Q22.3, R229.2
unnamed: Q23.3, Q24.1, R235.1
unnamed: Q24.3, R237.2
unnamed: Q25.3, Q26.1, R243.1
unnamed: Q26.3, R245.2
unnamed: Q27.3, Q28.1, R251.1
unnamed: Q28.3, R253.2
unnamed: Q29.3, Q30.1, R259.1
unnamed: Q30.3, R261.2
unnamed: Q31.3, Q32.1, R267.1
unnamed: Q32.3, R269.2
unnamed: R1.1, U1.6
unnamed: R5.2, U2.7
unnamed: R6.2, U2.3
unnamed: R11.1, U4.6
unnamed: R15.1, SW2.2, U3.3
unnamed: R19.2, TP37.1
unnamed: R23.2, TP39.1
unnamed: R29.1, X1.4
unnamed: R35.1, R41.2, U8.8
unnamed: R36.1, U8.1
unnamed: R37.1, U8.4
unnamed: R48.1, U5.6
unnamed: R49.2, U5.2, U5.3
unnamed: R61.1, R62.2, U9.20
unnamed: R63.2, U9.23
unnamed: R64.2, U9.22
unnamed: R65.1, U9.13
unnamed: R68.2, R69.1, R70.2, U10.3
unnamed: R70.1, R71.2, U10.1, U11.3
unnamed: R72.2, U11.4
unnamed: R73.1, R74.2, U12.20
unnamed: R75.2, U12.23
unnamed: R76.2, U12.22
unnamed: R77.1, U12.13
unnamed: R80.2, R81.1, R82.2, U13.3
unnamed: R82.1, R83.2, U13.1, U14.3
unnamed: R84.2, U14.4
unnamed: R85.1, U15.4
unnamed: R86.1, U15.5
unnamed: R87.1, U16.10
unnamed: R88.1, U16.9
unnamed: R89.1, U16.11
unnamed: R90.2, U16.12
unnamed: R91.2, U17.1
unnamed: R92.2, U18.1
unnamed: R316.1, U83.10
unnamed: R317.1, U83.9
unnamed: R318.1, U83.11
unnamed: R319.2, U83.12
unnamed: R321.1, R322.2, U84.7
unnamed: SW1.2, U3.6
VBUS: C174.1, C175.1, C176.1, C183.1, L3.2, R55.1, R56.1, U83.4, U83.5, U83.6, U84.1

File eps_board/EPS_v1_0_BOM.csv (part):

Reference, Quantity, Value, Footprint, Datasheet, Mfr. #, Order, Voltage
BT1 BT2 ,2,"Battery_Cell","footprint_custom:BatteryHolder_Keystone_54_v2_1x18650","https://www.keyelco.com/product.cfm/product_id/826","54","https://www.digikey.com/en/products/detail/keystone-electron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",""
C1 C2 C13 ,3,"0.01uF","Capacitor_SMD:C_0603_1608Metric_Pad1.05x0.95mm_HandSolder","~","CL10B103KB8NNNC","https://www.digikey.com/en/products/detail/samsung-electro-m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","50V"
C4 C5 C6 C7 C8 C9 C10 C11 C12 C16 C17 C18 C19 C20 C21 C24 C26 C29 C31 C36 C38 C47 C49 C50 C53 C55 C57 C58 C61 C63 C65 C66 C69 C71 C73 C74 C77 C79 C81 C82 C85 C87 C89 C90 C93 C95 C97 C98 C101 C103 C105 C106 C109 C111 C113 C114 C117 C119 C121 C122 C125 C127 C129 C130 C133 C135 C137 C138 C141 C143 C145 C146 C149 C151 C153 C154 C157 C159 C161 C162 C165 C167 C169 C170 C173 ,85,"0.1uF","Capacitor_SMD:C_0603_1608Metric_Pad1.05x0.95mm_HandSolder","~","CL10B104KA8NNNC","https://www.digikey.com/product-detail/en/samsung-electro-me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","25V"
C3 C15 C22 C25 C27 C30 C33 C40 C52 C60 C68 C76 C84 C92 C100 C108 C116 C124 C132 C140 C148 C156 C164 C172 C175 C179 C187 C188 C189 C190 C191 C192 ,32,"4.7uF","Capacitor_SMD:C_0603_1608Metric_Pad1.05x0.95mm_HandSolder","~","C1608X7S1A475K080AC","https://www.digikey.com/product-detail/en/tdk-corporation/C1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","10V"
C23 C28 C43 C182 ,4,"DNP","Capacitor_SMD:C_0603_1608Metric_Pad1.05x0.95mm_HandSolder","~"
C14 C34 C44 C45 C51 C59 C67 C75 C83 C91 C99 C107 C115 C123 C131 C139 C147 C155 C163 C171 C176 C184 ,22,"1uF","Capacitor_SMD:C_0603_1608Metric_Pad1.05x0.95mm_HandSolder","~","CL10B105KP8NFNC","https://www.digikey.com/product-detail/en/samsung-electro-me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","10V"
C35 C37 C177 C178 ,4,"22nF","Capacitor_SMD:C_0603_1608Metric_Pad1.05x0.95mm_HandSolder","~","GCM188R72A223KA37D","https://www.digikey.com/product-detail/en/murata-electronics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","100V"
C39 ,1,"4.7nF","Capacitor_SMD:C_0603_1608Metric_Pad1.05x0.95mm_HandSolder","~","885012206087","https://www.digikey.com/product-detail/en/w%C3%BCrth-elektro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","50V"
C32 C41 C174 C180 C183 C185 ,6,"47uF","Capacitor_SMD:C_1210_3225Metric_Pad1.42x2.65mm_HandSolder","~","GRM32EC81C476KE15L","https://www.digikey.com/product-detail/en/murata-electronics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","16V"
C42 C181 C186 ,3,"DNP","Capacitor_SMD:C_1210_3225Metric_Pad1.42x2.65mm_HandSolder","~"
C46 C48 C54 C56 C62 C64 C70 C72 C78 C80 C86 C88 C94 C96 C102 C104 C110 C112 C118 C120 C126 C128 C134 C136 C142 C144 C150 C152 C158 C160 C166 C168 ,32,"DNP","Capacitor_SMD:C_0603_1608Metric","~"
D10 D11 D12 D13 D14 D15 D16 D17 ,8,"NRVB120VLSFT1G","footprint_custom:D_SOD-123FL_handsolder","https://www.onsemi.com/pub/Collateral/MBR120VLSFT1-D.PDF","NRVB120VLSFT1G","https://www.digikey.com/product-detail/en/on-semiconductor/N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",""
D6 D7 D8 D18 ,4,"ESD9B5.0ST5G","Diode_SMD:D_SOD-923","https://www.onsemi.com/pub/Collateral/ESD9B-D.PDF","ESD9B5.0ST5G","https://www.digikey.com/product-detail/en/on-semiconductor/E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",""
D1 D19 ,2,"LED_SMD_RED","LED_SMD:LED_0603_1608Metric_Pad1.05x0.95mm_HandSolder","https://katalog.we-online.de/led/datasheet/150060RS75000.pdf","150060RS75000","https://www.digikey.com/product-detail/en/w%C3%BCrth-elektro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",""
D2 ,1,"LED_SMD_GREEN","LED_SMD:LED_0603_1608Metric_Pad1.05x0.95mm_HandSolder","https://katalog.we-online.de/led/datasheet/150060VS75000.pdf","150060VS75000","https://www.digikey.com/product-detail/en/w%C3%BCrth-elektro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",""
D3 D4 D5 ,3,"LED_SMD_YELLOW","LED_SMD:LED_0603_1608Metric_Pad1.05x0.95mm_HandSolder","https://www.digikey.com/Web%20Export/Common/icons/datasheet.png","150060YS75000","https://www.digikey.com/product-detail/en/w%C3%BCrth-elektro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",""
D9 ,1,"NUP2105L","Package_TO_SOT_SMD:SOT-23","http://www.onsemi.com/pub_link/Collateral/NUP2105L-D.PDF","NUP2105LT1G","https://www.digikey.com/product-detail/en/on-semiconductor/N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",""
F1 F2 ,2,"Polyfuse","Fuse:Fuse_1206_3216Metric_Pad1.42x1.75mm_HandSolder","~","1206L380SLTHYR","https://www.digikey.com/en/products/detail/littelfuse-inc/12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",""
FID4 ,1,"Fiducial","Calibration_Scale:Gauge_10mm_Type1_SilkScreenTop","~"
H1 ,1,"MountingHole","MountingHole:MountingHole_2.1mm","~"
H2 H3 H4 H5 ,4,"MountingHole_Pad","MountingHole:MountingHole_3.2mm_M3_Pad_Via","~"
J1 J3 J5 J7 J8 J9 ,6,"Conn_01x04","Connector_PinHeader_2.54mm:PinHeader_1x04_P2.54mm_Vertical","~"
J12 ,1,"Conn_01x05","Connector_PinHeader_2.54mm:PinHeader_1x05_P2.54mm_Vertical","~","PH1-05-UA","https://www.digikey.com/product-detail/en/adam-tech/PH1-05-U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",""
J13 ,1,"Conn_01x04_Male","Connector_PinHeader_2.54mm:PinHeader_1x04_P2.54mm_Vertical","~","PREC004SBAN-M71RC","https://www.digikey.com/product-detail/en/sullins-connector-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",""
J14 ,1,"USB_B_Micro","Connector_USB:USB_Micro-B_Amphenol_10103594-0001LF_Horizontal","~","10103594-0001LF","https://www.digikey.com/en/products/detail/amphenol-icc-fci/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",""
J2 J4 ,2,"Conn_01x02_Female","Connector_PinHeader_1.27mm:PinHeader_1x02_P1.27mm_Vertical","~"
J6 ,1,"Conn_02x20_Odd_Even","Connector_PinHeader_2.54mm:PinHeader_2x20_P2.54mm_Vertical","~","ESQ-120-13-T-D","https://www.digikey.com/product-detail/en/samtec-inc/ESQ-120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",""
L1 L2 ,2,"4.7uH","Inductor_SMD:L_Coilcraft_LPS4018","~","LPS4018-472","https://www.coilcraft.com/en-us/products/power/shielded-indu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",""
L3 ,1,"2.2uH","Inductor_SMD:L_Coilcraft_XAL5030","https://www.coilcraft.com/en-us/products/power/shielded-indu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","XAL5030-222","https://www.coilcraft.com/en-us/products/power/shielded-indu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",""
Q1 Q2 Q3 Q4 Q5 Q6 Q7 Q8 Q9 Q10 Q11 Q12 Q13 Q14 Q15 Q16 Q17 Q18 Q19 Q20 Q21 Q22 Q23 Q24 Q25 Q26 Q27 Q28 Q29 Q30 Q31 Q32 ,32,"2N7002K","Package_TO_SOT_SMD:SOT-23","https://www.diodes.com/assets/Datasheets/ds30896.pdf","2N7002K-7","https://www.digikey.com/en/products/detail/diodes-incorporat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",""
R5 R6 R8 R10 R12 R13 R14 R16 R17 R18 R32 R33 R41 R42 R46 R47 R50 R51 R52 R59 R60 R65 R68 R77 R80 R144 R152 R160 R168 R176 R184 R192 R200 R208 R216 R224 R232 R240 R248 R256 R264 R306 R307 R308 R309 R310 R311 R312 R313 R314 R315 R320 ,52,"100K","Resistor_SMD:R_0603_1608Metric_Pad1.05x0.95mm_HandSolder","~","RMCF0603FT100K","https://www.digikey.com/en/products/detail/stackpole-electro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",""
R101 R103 R105 R123 R125 R127 R129 R135 R137 R139 R141 ,11,"140K","Resistor_SMD:R_0603_1608Metric_Pad1.05x0.95mm_HandSolder","~","RK73H1JTTD1403F","https://www.digikey.com/en/products/detail/koa-speer-electro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",""
R111 R117 ,2,"698K","Resistor_SMD:R_0603_1608Metric_Pad1.05x0.95mm_HandSolder","~","RMCF0603FT698K","https://www.digikey.com/en/products/detail/stackpole-electro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",""
R113 R115 ,2,"1.5M","Resistor_SMD:R_0603_1608Metric_Pad1.05x0.95mm_HandSolder","~","RC0603FR-071M5L","https://www.digikey.com/en/products/detail/yageo/RC0603FR-07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",""
R15 ,1,"8.85K","Resistor_SMD:R_0603_1608Metric_Pad1.05x0.95mm_HandSolder","~","RMCF0603FT8K87","https://www.digikey.com/product-detail/en/stackpole-electron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",""
R19 R20 R21 R22 R23 ,5,"49.9","Resistor_SMD:R_0603_1608Metric_Pad1.05x0.95mm_HandSolder","https://www.mouser.com/datasheet/2/392/susumu_RR_Data_Sheet-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","RR0816Q-49R9-D-68R ","https://www.mouser.com/ProductDetail/Susumu/RR0816Q-49R9-D-6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",""
R322 ,1,"137K","Resistor_SMD:R_0603_1608Metric_Pad1.05x0.95mm_HandSolder","~","RMCF0603FT137K","https://www.digikey.com/en/products/detail/stackpole-electro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",""
R323 R324 R325 R326 ,4,"1","Resistor_SMD:R_0603_1608Metric_Pad1.05x0.95mm_HandSolder","~","RK73H1JTTD1R00F","https://www.digikey.com/en/products/detail/koa-speer-electro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",""
R1 R29 R30 R31 R35 R36 R37 R38 R57 R58 R87 R88 R89 R90 R143 R149 R151 R157 R159 R165 R167 R173 R175 R181 R183 R189 R191 R197 R199 R205 R207 R213 R215 R221 R223 R229 R231 R237 R239 R245 R247 R253 R255 R261 R263 R269 R304 R305 R316 R317 R318 R319 R327 ,53,"0","Resistor_SMD:R_0603_1608Metric_Pad1.05x0.95mm_HandSolder","~","RK73Z1JTTD","https://www.digikey.com/product-detail/en/koa-speer-electron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",""
R24 R25 R26 R27 R28 R329 ,6,"330","Resistor_SMD:R_0603_1608Metric_Pad1.05x0.95mm_HandSolder","https://www.mouser.com/datasheet/2/427/dcrcwe3-1762152.pdf","CRCW0603330RJNEA","https://www.mouser.com/ProductDetail/Vishay-Dale/CRCW0603330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",""
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
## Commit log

2020-08-09 initial
2020-08-30 Initial EPS. Each solar input has a regulator.
2020-08-30 EPS with schottky diodes & 1 regulator
2020-08-30 Removed unecessary footprint lib
2020-10-09 Progress on EPS
2020-10-16 Essentially done with EPS schematic
2020-10-28 EPS layout in progress
2020-11-03 EPS V1.0 Complete
2021-03-14 Sun Sensor Test board
2021-03-19 Update Avionics part names to match KiCad update. Update Avionics board to use new interboard connector
2021-04-30 Avionics Board layout done
2021-07-09 Update README, add pictures
2021-08-25 openlst-hw submodule
2021-10-17 Radio Schematic update complete.
2021-11-17 Radio layout complete, except for minor artwork touchups
2021-11-29 Finished radio artwork
2021-12-18 Add EPS & Avionics BOM
2022-01-03 Bump openlst-hw
